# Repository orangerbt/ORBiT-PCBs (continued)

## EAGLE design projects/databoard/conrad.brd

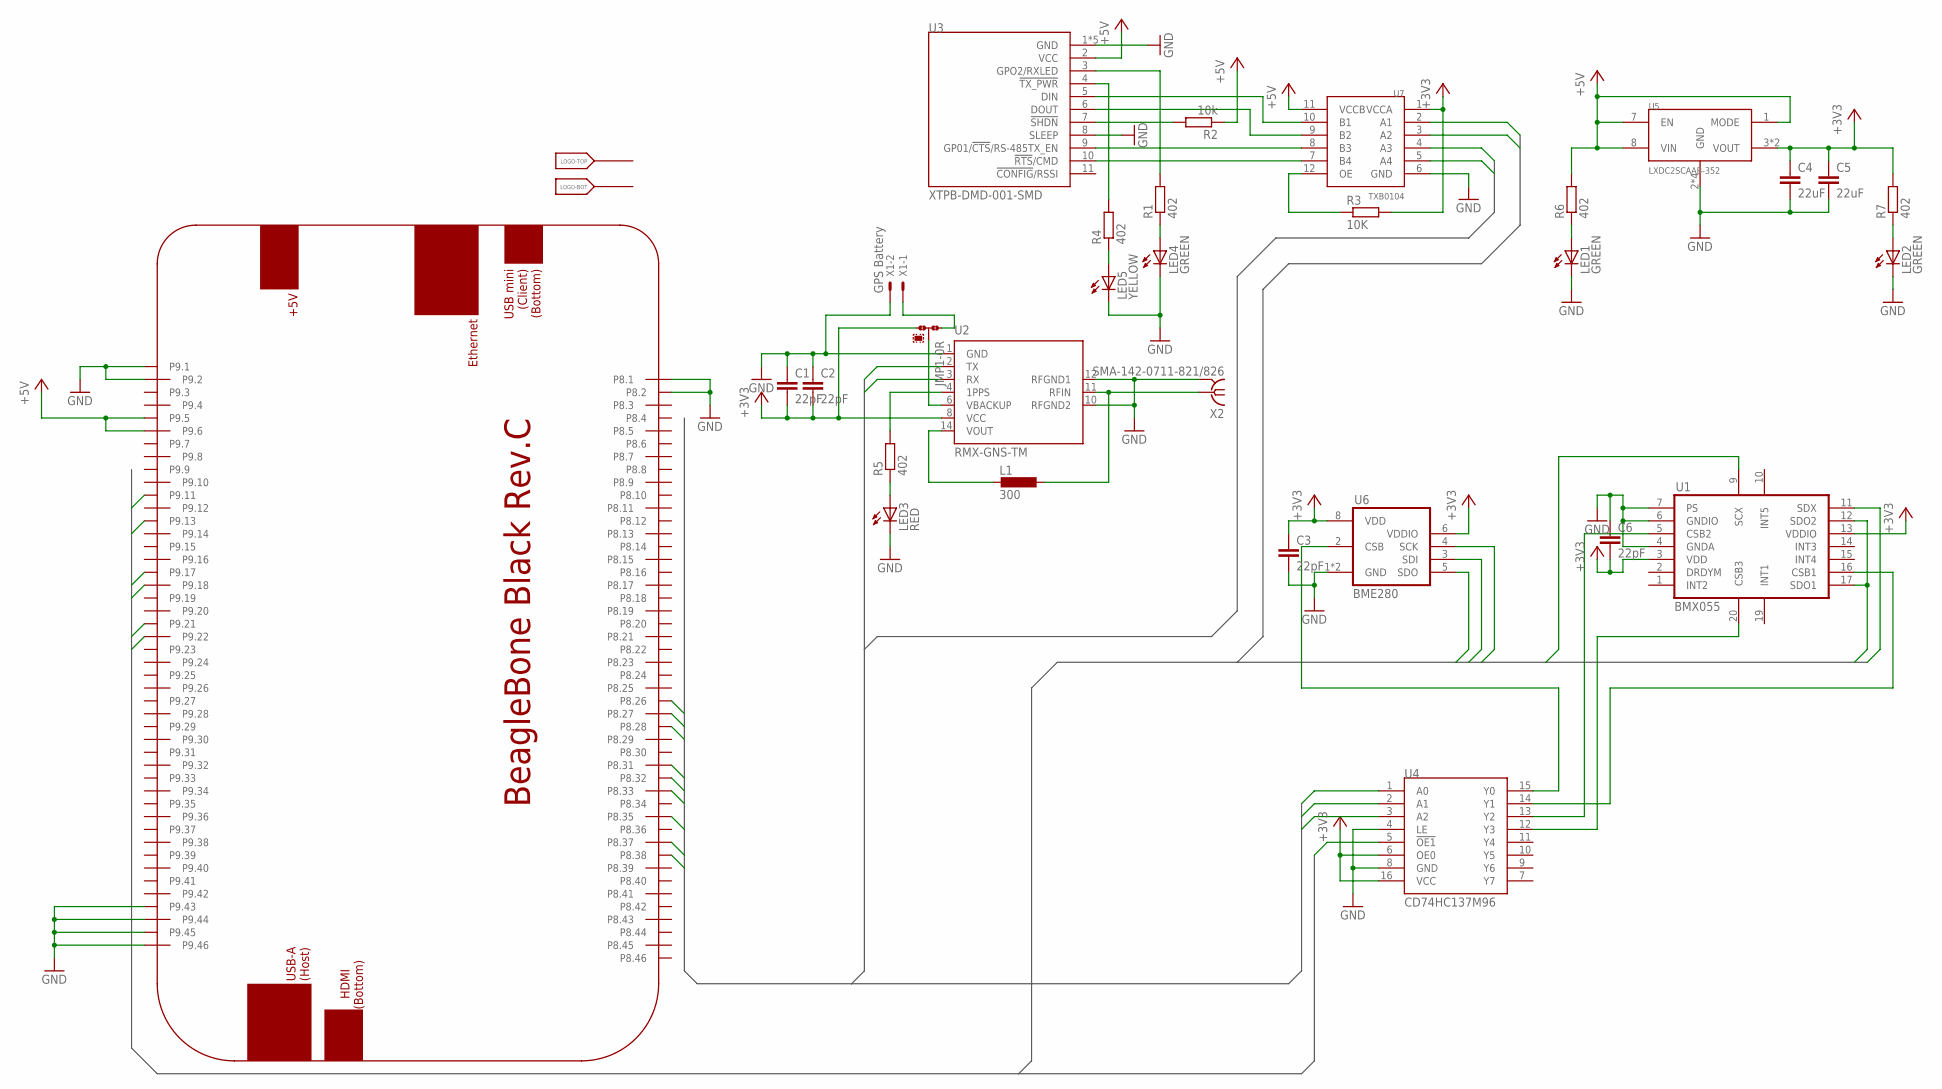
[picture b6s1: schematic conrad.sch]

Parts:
C1, C2, C3, C6: 22pF; C0603K
C4, C5: 22uF; C0603K
JMP1: 0R-JUMPB; B0R-JMP
L1: 300; L0402
LED1, LED2, LED4: GREEN; SML0805
LED3: RED; SML0805
LED5: YELLOW; SML0805
LOGO: SU_LOGO-DUMMY; SU_LOGO_DS
PCB1: BEAGLEBONE_BLACK_CAPE
R1, R4, R5, R6, R7: 402; R0603
R2: 10k; R0603
R3: 10K; R0603
U1: BMX055
U2: RMX-GNS-TM; RMX-GNSS-TM
U3: XTPB-DMD-001-SMD; XTP9B-DMS-001-SMD
U4: CD74HC137M96; SO-16
U5: LXDC2SCAAB-352
U6: BME280
U7: TXB0104; R-PUQFN-N12
X1: GPS Battery; 15-91-02
X2: SMA-142-0711-821/826; J502-ND-142-0711-821/826

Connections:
+3V3: C1.2, C2.2, C3.1, C4.1, C5.1, C6.2, JMP1.3, R3.2, R7.2, U1.3 (VDD), U1.13 (VDDIO), U2.8 (VCC), U4.6 (OE0), U4.16 (VCC), U5.3 (VOUT), U5.4 (VOUT), U6.6 (VDDIO), U6.8 (VDD), U7.1 (VCCA)
+5V: PCB1.P9.5, PCB1.P9.6, R2.1, R6.2, U3.2 (VCC), U5.1 (MODE), U5.7 (EN), U5.8 (VIN), U7.11 (VCCB)
GND: C1.1, C2.1, C3.2, C4.2, C5.2, C6.1, LED1.C, LED2.C, LED3.C, LED4.C, LED5.C, PCB1.P8.1, PCB1.P8.2, PCB1.P9.1, PCB1.P9.2, PCB1.P9.43, PCB1.P9.44, PCB1.P9.45, PCB1.P9.46, U1.4 (GNDA), U1.6 (GNDIO), U1.7 (PS), U2.1 (GND), U2.10 (RFGND2), U2.12 (RFGND1), U3.1 (GND), U3.8 (SLEEP), U3.P$1 (GND), U3.P$2 (GND), U3.P$3 (GND), U3.P$4 (GND), U4.4 (LE), U4.8 (GND), U5.2 (GND), U5.5 (GND), U5.6 (GND), U5.9 (GND), U6.1 (GND), U6.7 (GND), U7.6 (GND), X1.2, X2.G@1 (2), X2.G@2 (2), X2.G@3 (2), X2.G@4 (2)
unnamed: R3.1, U7.12 (OE)
unnamed: LED4.A, R1.1
unnamed: U3.6 (DOUT), U7.9 (B2)
unnamed: R4.2, U3.4 (!TX_PWR!)
unnamed: L1.1, U2.11 (RFIN), X2.1
unnamed: JMP1.1, X1.1
unnamed: U4.15 (Y0), U6.2 (CSB)
unnamed: U1.5 (CSB2), U4.13 (Y2)
unnamed: L1.2, U2.14 (VOUT)
unnamed: U1.16 (CSB1), U4.14 (Y1)
unnamed: R1.2, U3.3 (GPO2/RXLED)
unnamed: U1.20 (CSB3), U4.12 (Y3)
unnamed: R5.2, U2.4 (1PPS)
unnamed: LED5.A, R4.1
unnamed: R2.2, U3.7 (!SHDN!)
unnamed: LED3.A, R5.1
unnamed: LED1.A, R6.1
unnamed: LED2.A, R7.1
SPI0_CS0: PCB1.P9.17, U4.5 (!OE1!)
SPI0_D0: PCB1.P9.21, U1.12 (SDO2), U1.17 (SDO1), U6.5 (SDO)
SPI0_D1: PCB1.P9.18, U1.11 (SDX), U6.3 (SDI)
SPI0_SCLK: PCB1.P9.22, U1.9 (SCX), U6.4 (SCK)
SPI_CSB26: PCB1.P8.26, U4.1 (A0)
SPI_CSB27: PCB1.P8.27, U4.2 (A1)
SPI_CSB28: PCB1.P8.28, U4.3 (A2)
UART4_CTSN: PCB1.P8.35, U7.4 (A3)
UART4_CTSN_HV: U3.9 (GP01/!CTS!/RS-485TX_EN), U7.8 (B3)
UART4_RTSN: PCB1.P8.33, U7.5 (A4)
UART4_RTSN_HV: U3.10 (!RTS!/CMD), U7.7 (B4)
UART4_RXD: PCB1.P9.11, U7.3 (A2)
UART4_TXD: PCB1.P9.13, U7.2 (A1)
UART4_TXD-HV: U3.5 (DIN), U7.10 (B1)
UART5_CTSN: PCB1.P8.31
UART5_RTSN: PCB1.P8.32
UART5_RXD: PCB1.P8.38, U2.2 (TX)
UART5_TXD: PCB1.P8.37, U2.3 (RX)
VBACKUP: JMP1.2, U2.6 (VBACKUP)

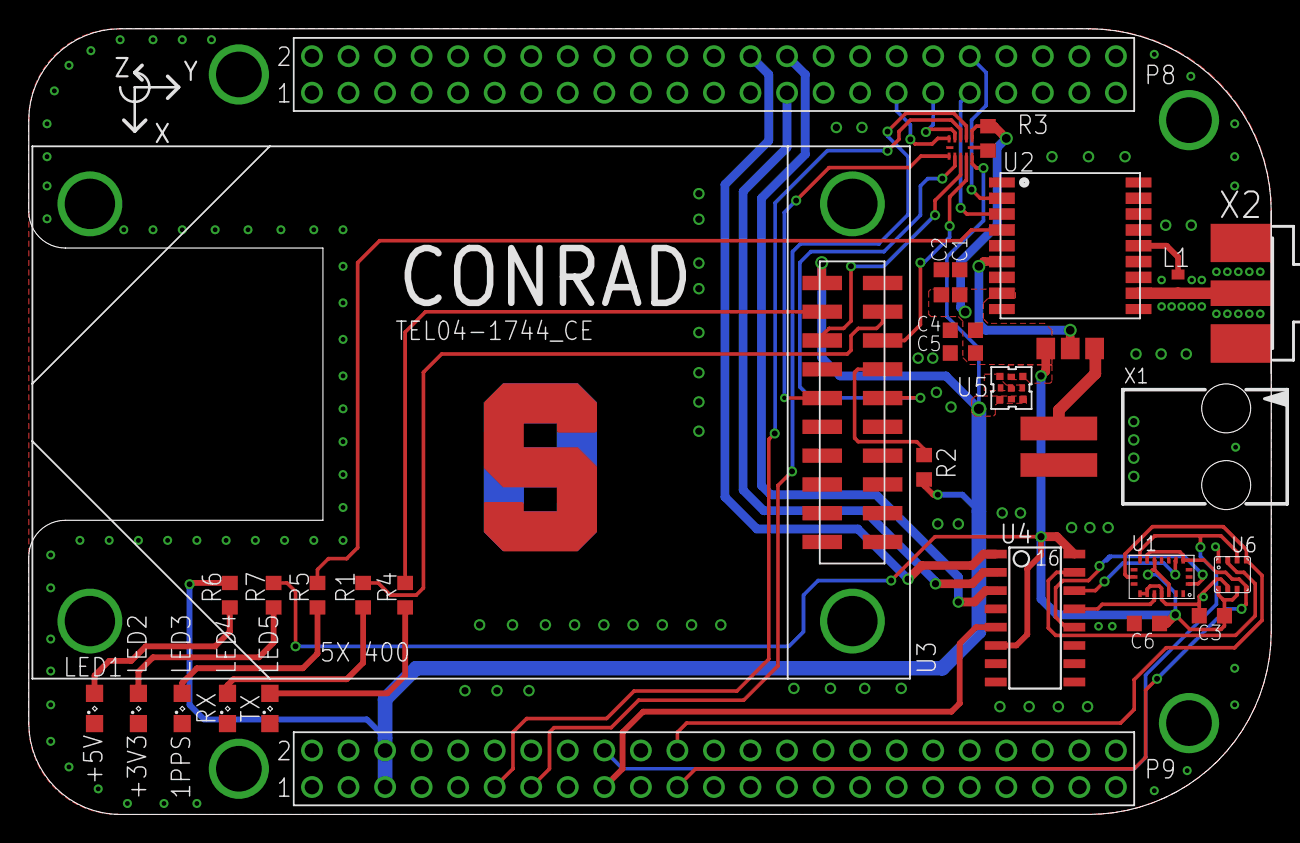
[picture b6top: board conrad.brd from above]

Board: 2 copper layers, 86.4 x 54.6 mm, 31 parts (0 on the bottom side), 38 nets.

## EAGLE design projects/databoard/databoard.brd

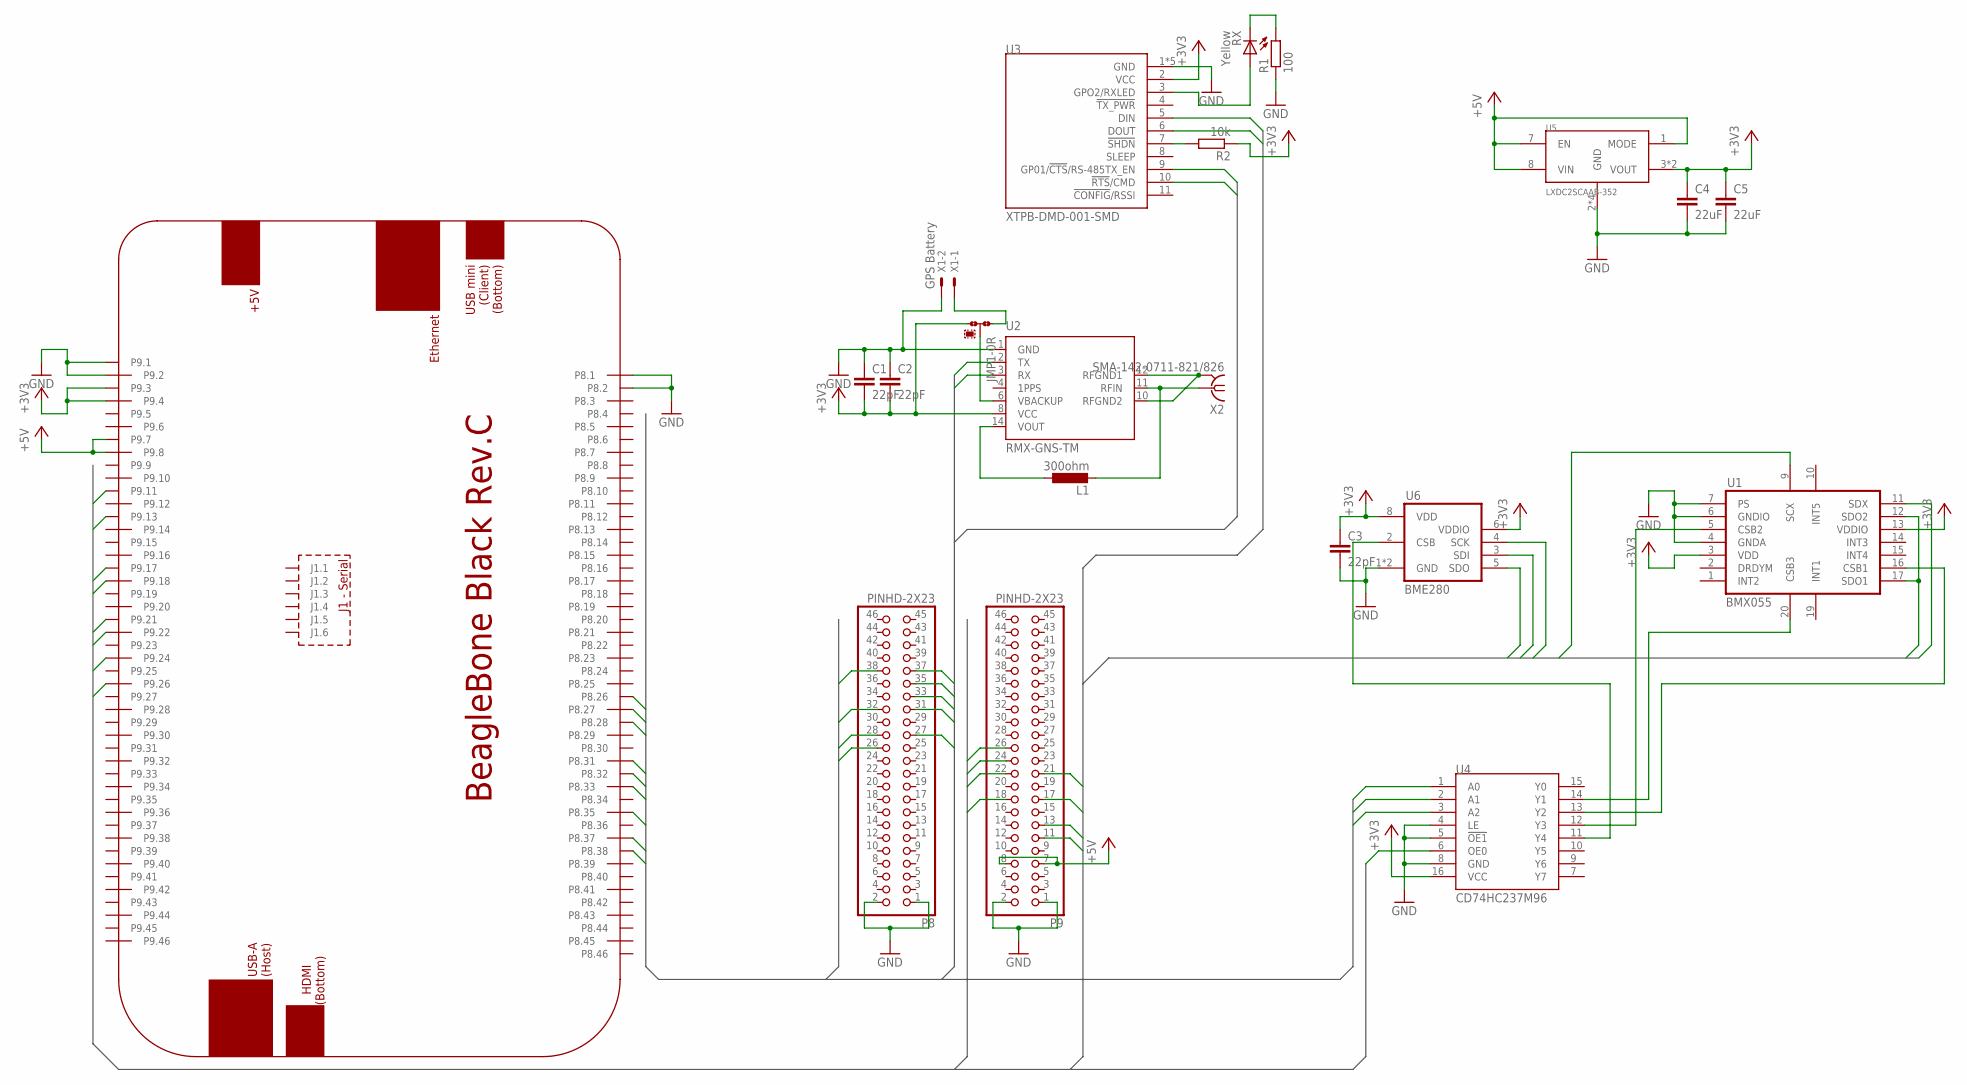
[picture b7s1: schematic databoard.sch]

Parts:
C1, C2, C3: 22pF; C0603K
C4, C5: 22uF; C0603K
JMP1: 0R-JUMPB; B0R-JMP
L1: 300ohm; L1206
P8, P9: PINHD-2X23; 2X23
R1: 100; R0402
R2: 10k; R0402
RX: Yellow; SML0805
U1: BMX055
U2: RMX-GNS-TM; RMX-GNSS-TM
U3: XTPB-DMD-001-SMD; XTP9B-DMS-001-SMD
U4: CD74HC237M96; SO-16
U5: LXDC2SCAAB-352
U6: BME280
X1: GPS Battery; 15-91-02
X2: SMA-142-0711-821/826; J502-ND-142-0711-821/826

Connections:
+3V3: C1.2, C2.2, C3.1, C4.1, C5.1, JMP1.3, R2.1, U1.3 (VDD), U1.13 (VDDIO), U2.8 (VCC), U3.2 (VCC), U4.16 (VCC), U5.3 (VOUT), U5.4 (VOUT), U6.6 (VDDIO), U6.8 (VDD)
+5V: P9.7, P9.8, U5.1 (MODE), U5.7 (EN), U5.8 (VIN)
GND: C1.1, C2.1, C3.2, C4.2, C5.2, P8.1, P8.2, P9.1, P9.2, R1.1, U1.4 (GNDA), U1.6 (GNDIO), U1.7 (PS), U2.1 (GND), U3.1 (GND), U3.P$1 (GND), U3.P$2 (GND), U3.P$3 (GND), U3.P$4 (GND), U4.4 (LE), U4.5 (!OE1!), U4.8 (GND), U5.2 (GND), U5.5 (GND), U5.6 (GND), U5.9 (GND), U6.1 (GND), U6.7 (GND), X1.2
I2C1_SCL: P9.24
I2C1_SDA: P9.26
unnamed: L1.2, U2.11 (RFIN), X2.1
unnamed: JMP1.1, X1.1
unnamed: U4.11 (Y4), U6.2 (CSB)
unnamed: U1.5 (CSB2), U4.12 (Y3)
unnamed: L1.1, U2.14 (VOUT)
unnamed: U1.16 (CSB1), U4.13 (Y2)
unnamed: RX.A, U3.3 (GPO2/RXLED)
unnamed: U1.20 (CSB3), U4.14 (Y1)
unnamed: R1.2, RX.C
unnamed: R2.2, U3.7 (!SHDN!)
RFGND1: U2.10 (RFGND2), U2.12 (RFGND1), X2.G@1 (2), X2.G@2 (2), X2.G@3 (2), X2.G@4 (2)
SPI0_CS0: P9.17, U4.6 (OE0)
SPI0_D0: P9.21, U1.12 (SDO2), U1.17 (SDO1), U6.5 (SDO)
SPI0_D1: P9.18, U1.11 (SDX), U6.3 (SDI)
SPI0_SCLK: P9.22, U1.9 (SCX), U6.4 (SCK)
SPI_CSB26: P8.26, U4.1 (A0)
SPI_CSB27: P8.27, U4.2 (A1)
SPI_CSB28: P8.28, U4.3 (A2)
UART4_CTSN: P8.35, U3.9 (GP01/!CTS!/RS-485TX_EN)
UART4_RTSN: P8.33, U3.10 (!RTS!/CMD)
UART4_RXD: P9.11, U3.6 (DOUT)
UART4_TXD: P9.13, U3.5 (DIN)
UART5_CTSN: P8.31
UART5_RTSN: P8.32
UART5_RXD: P8.38, U2.3 (RX)
UART5_TXD: P8.37, U2.2 (TX)
VBACKUP: JMP1.2, U2.6 (VBACKUP)

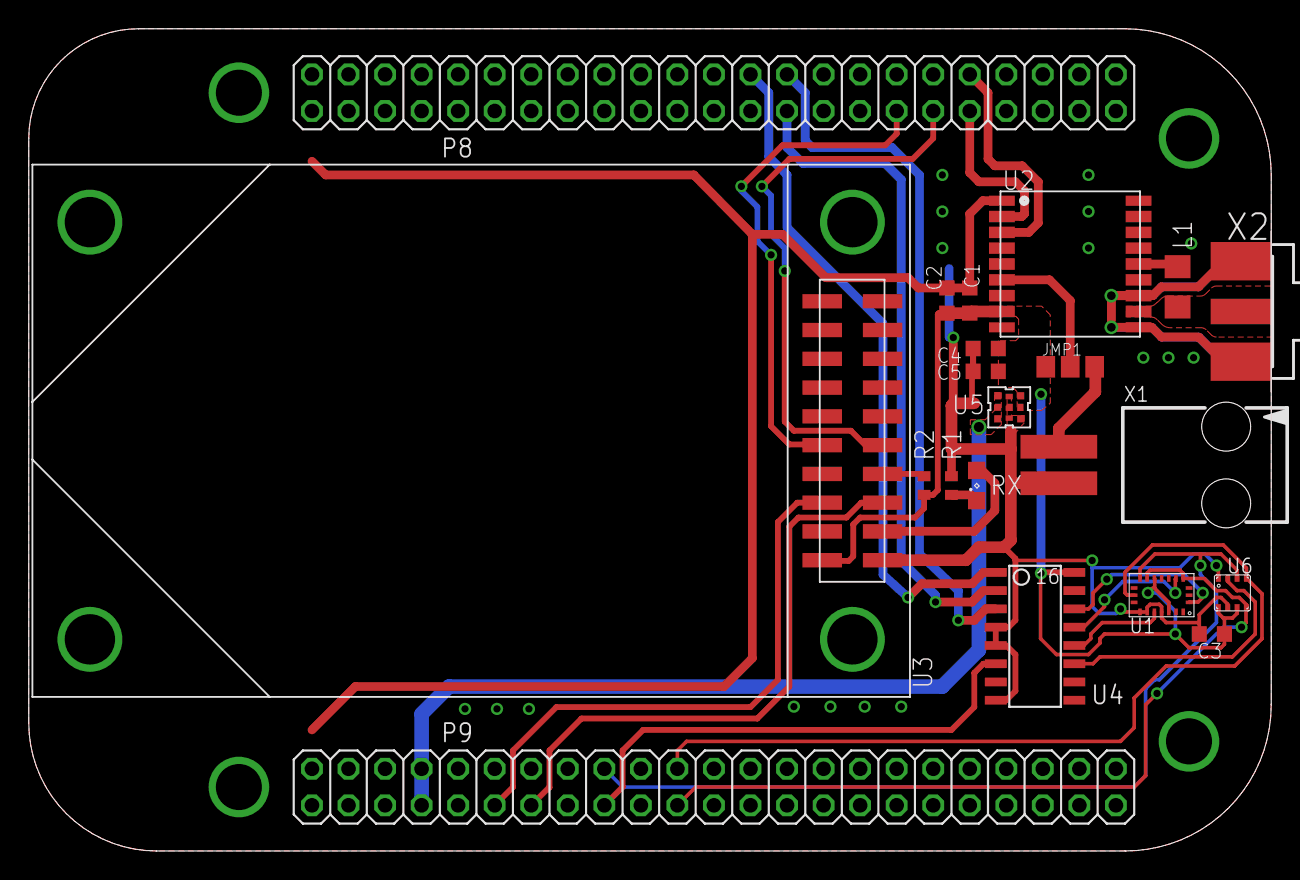
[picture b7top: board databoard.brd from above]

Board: 2 copper layers, 86.4 x 57.2 mm, 20 parts (0 on the bottom side), 28 nets.

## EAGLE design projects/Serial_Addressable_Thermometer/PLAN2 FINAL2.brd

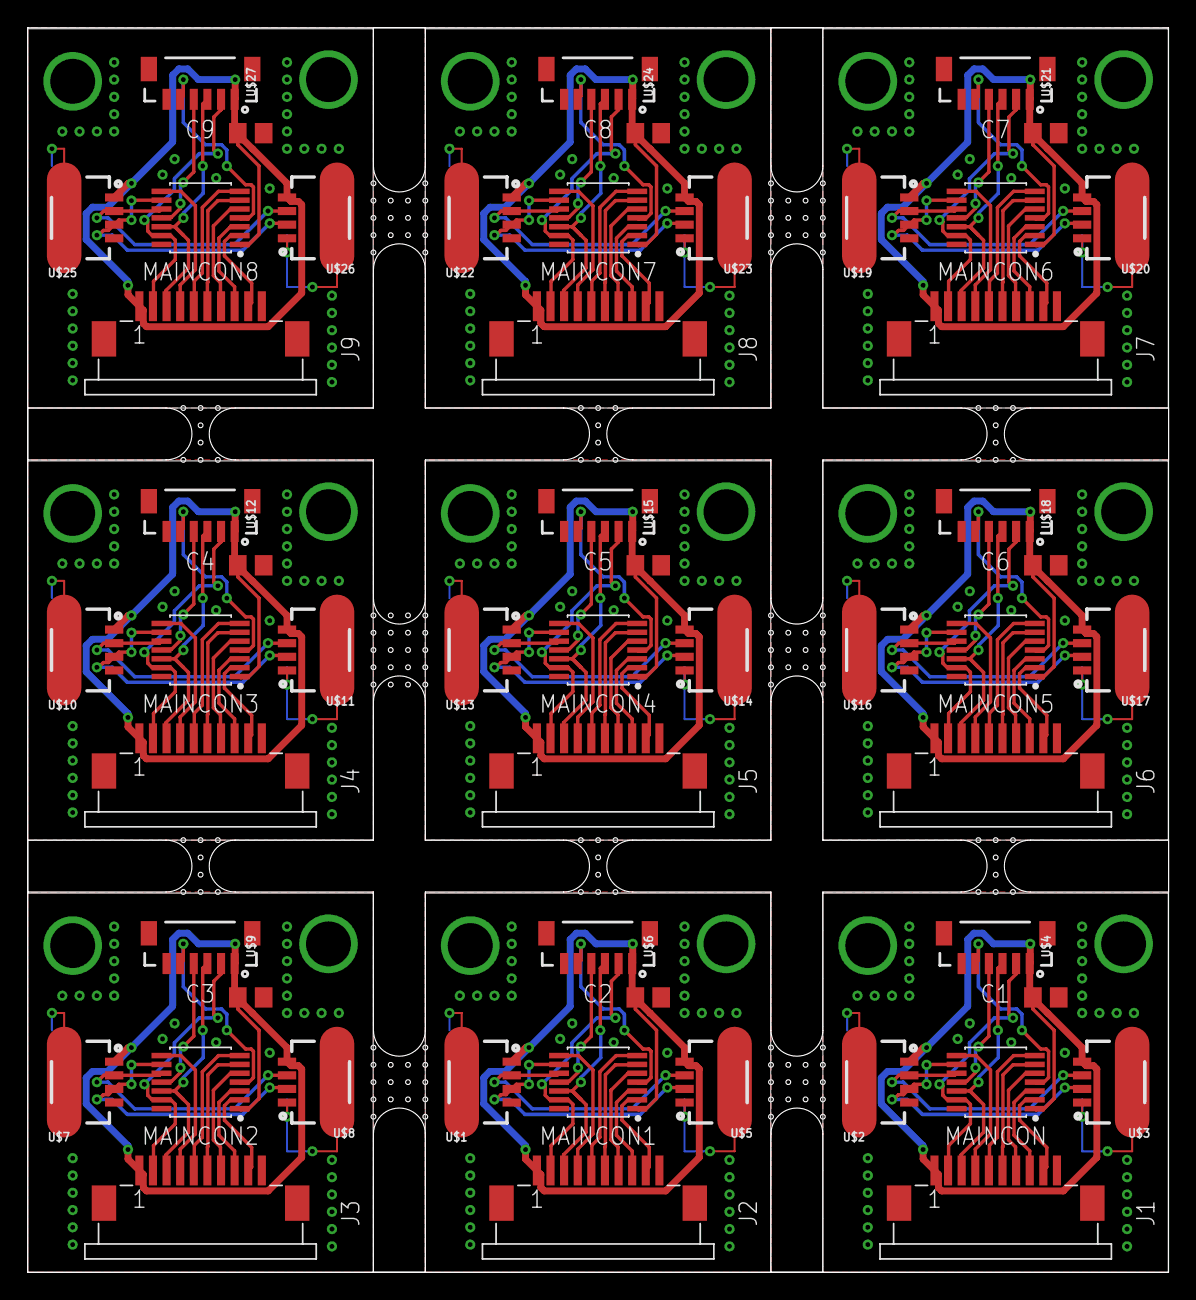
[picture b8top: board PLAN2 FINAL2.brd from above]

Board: 2 copper layers, 83.8 x 91.4 mm, 54 parts (0 on the bottom side), 126 nets.

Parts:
C1, C2, C3, C4, C5, C6, C7, C8, C9: 47u; C0805
J1, J2, J3, J4, J5, J6, J7, J8, J9: analog; 68611014422
MAINCON, MAINCON1, MAINCON2, MAINCON3, MAINCON4, MAINCON5, MAINCON6, MAINCON7, MAINCON8: PIC16F18424; 14-TSSOP
U$1, U$2, U$7, U$10, U$13, U$16, U$19, U$22, U$25: IIC1; JST_ZH_4PIN
U$3, U$5, U$8, U$11, U$14, U$17, U$20, U$23, U$26: IIC2; JST_ZH_4PIN
U$4, U$6, U$9, U$12, U$15, U$18, U$21, U$24, U$27: programming; JST_ZH_6PIN

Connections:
+5V: C1.1, J1.1, MAINCON.1, U$2.1, U$3.4, U$4.1
+5V1: C2.1, J2.1, MAINCON1.1, U$1.1, U$5.4, U$6.1
+5V2: C3.1, J3.1, MAINCON2.1, U$7.1, U$8.4, U$9.1
+5V3: C4.1, J4.1, MAINCON3.1, U$10.1, U$11.4, U$12.1
+5V4: C5.1, J5.1, MAINCON4.1, U$13.1, U$14.4, U$15.1
+5V5: C6.1, J6.1, MAINCON5.1, U$16.1, U$17.4, U$18.1
+5V6: C7.1, J7.1, MAINCON6.1, U$19.1, U$20.4, U$21.1
+5V7: C8.1, J8.1, MAINCON7.1, U$22.1, U$23.4, U$24.1
+5V8: C9.1, J9.1, MAINCON8.1, U$25.1, U$26.4, U$27.1
AD1: J1.2, MAINCON.13, U$4.2
AD2: J1.3, MAINCON.12, U$4.3
AD3: J1.4, MAINCON.8
AD4: J1.5, MAINCON.7
AD5: J1.6, MAINCON.6
AD6: J1.7, MAINCON.5
AD7: J1.8, MAINCON.3
AD8: J1.9, MAINCON.2
AD9: J2.4, MAINCON1.8
AD10: J2.5, MAINCON1.7
AD11: J2.6, MAINCON1.6
AD12: J2.7, MAINCON1.5
AD13: J2.8, MAINCON1.3
AD14: J2.9, MAINCON1.2
AD15: J2.2, MAINCON1.13, U$6.2
AD16: J2.3, MAINCON1.12, U$6.3
AD17: J3.4, MAINCON2.8
AD18: J3.5, MAINCON2.7
AD19: J3.6, MAINCON2.6
AD20: J3.7, MAINCON2.5
AD21: J3.8, MAINCON2.3
AD22: J3.9, MAINCON2.2
AD23: J3.2, MAINCON2.13, U$9.2
AD24: J3.3, MAINCON2.12, U$9.3
AD25: J4.4, MAINCON3.8
AD26: J4.5, MAINCON3.7
AD27: J4.6, MAINCON3.6
AD28: J4.7, MAINCON3.5
AD29: J4.8, MAINCON3.3
AD30: J4.9, MAINCON3.2
AD31: J4.2, MAINCON3.13, U$12.2
AD32: J4.3, MAINCON3.12, U$12.3
AD33: J5.4, MAINCON4.8
AD34: J5.5, MAINCON4.7
AD35: J5.6, MAINCON4.6
AD36: J5.7, MAINCON4.5
AD37: J5.8, MAINCON4.3
AD38: J5.9, MAINCON4.2
AD39: J5.2, MAINCON4.13, U$15.2
AD40: J5.3, MAINCON4.12, U$15.3
AD41: J6.4, MAINCON5.8
AD42: J6.5, MAINCON5.7
AD43: J6.6, MAINCON5.6
AD44: J6.7, MAINCON5.5
AD45: J6.8, MAINCON5.3
AD46: J6.9, MAINCON5.2
AD47: J6.2, MAINCON5.13, U$18.2
AD48: J6.3, MAINCON5.12, U$18.3
AD49: J7.4, MAINCON6.8
AD50: J7.5, MAINCON6.7
AD51: J7.6, MAINCON6.6
AD52: J7.7, MAINCON6.5
AD53: J7.8, MAINCON6.3
AD54: J7.9, MAINCON6.2
AD55: J7.2, MAINCON6.13, U$21.2
AD56: J7.3, MAINCON6.12, U$21.3
AD57: J8.4, MAINCON7.8
AD58: J8.5, MAINCON7.7
AD59: J8.6, MAINCON7.6
AD60: J8.7, MAINCON7.5
AD61: J8.8, MAINCON7.3
AD62: J8.9, MAINCON7.2
AD63: J8.2, MAINCON7.13, U$24.2
AD64: J8.3, MAINCON7.12, U$24.3
AD65: J9.4, MAINCON8.8
AD66: J9.5, MAINCON8.7
AD67: J9.6, MAINCON8.6
AD68: J9.7, MAINCON8.5
AD69: J9.8, MAINCON8.3
AD70: J9.9, MAINCON8.2
AD71: J9.2, MAINCON8.13, U$27.2
AD72: J9.3, MAINCON8.12, U$27.3
GND: C1.2, J1.10, MAINCON.14, U$2.4, U$2.NC1, U$2.NC2, U$3.1, U$3.NC1, U$3.NC2, U$4.6, U$4.P$1
GND1: C2.2, J2.10, MAINCON1.14, U$1.4, U$1.NC1, U$1.NC2, U$5.1, U$5.NC1, U$5.NC2, U$6.6, U$6.P$1
GND2: C3.2, J3.10, MAINCON2.14, U$7.4, U$7.NC1, U$7.NC2, U$8.1, U$8.NC1, U$8.NC2, U$9.6, U$9.P$1
GND3: C4.2, J4.10, MAINCON3.14, U$10.4, U$10.NC1, U$10.NC2, U$11.1, U$11.NC1, U$11.NC2, U$12.6, U$12.P$1
GND4: C5.2, J5.10, MAINCON4.14, U$13.4, U$13.NC1, U$13.NC2, U$14.1, U$14.NC1, U$14.NC2, U$15.6, U$15.P$1
GND5: C6.2, J6.10, MAINCON5.14, U$16.4, U$16.NC1, U$16.NC2, U$17.1, U$17.NC1, U$17.NC2, U$18.6, U$18.P$1
GND6: C7.2, J7.10, MAINCON6.14, U$19.4, U$19.NC1, U$19.NC2, U$20.1, U$20.NC1, U$20.NC2, U$21.6, U$21.P$1
GND7: C8.2, J8.10, MAINCON7.14, U$22.4, U$22.NC1, U$22.NC2, U$23.1, U$23.NC1, U$23.NC2, U$24.6, U$24.P$1
GND8: C9.2, J9.10, MAINCON8.14, U$25.4, U$25.NC1, U$25.NC2, U$26.1, U$26.NC1, U$26.NC2, U$27.6, U$27.P$1
unnamed: MAINCON1.11, U$6.4
unnamed: MAINCON1.4, U$6.5
unnamed: MAINCON.11, U$4.4
unnamed: MAINCON.4, U$4.5
unnamed: MAINCON2.11, U$9.4
unnamed: MAINCON2.4, U$9.5
unnamed: MAINCON3.11, U$12.4
unnamed: MAINCON3.4, U$12.5
unnamed: MAINCON4.11, U$15.4
unnamed: MAINCON4.4, U$15.5
unnamed: MAINCON5.11, U$18.4
unnamed: MAINCON5.4, U$18.5
unnamed: MAINCON6.11, U$21.4
unnamed: MAINCON6.4, U$21.5
unnamed: MAINCON7.11, U$24.4
unnamed: MAINCON7.4, U$24.5
unnamed: MAINCON8.11, U$27.4
unnamed: MAINCON8.4, U$27.5
SCL: MAINCON.10, U$2.2, U$3.3
SCL1: MAINCON1.10, U$1.2, U$5.3
SCL2: MAINCON2.10, U$7.2, U$8.3
SCL3: MAINCON3.10, U$10.2, U$11.3
SCL4: MAINCON4.10, U$13.2, U$14.3
SCL5: MAINCON5.10, U$16.2, U$17.3
SCL6: MAINCON6.10, U$19.2, U$20.3
SCL7: MAINCON7.10, U$22.2, U$23.3
SCL8: MAINCON8.10, U$25.2, U$26.3
SDA: MAINCON.9, U$2.3, U$3.2
SDA1: MAINCON1.9, U$1.3, U$5.2
SDA2: MAINCON2.9, U$7.3, U$8.2
SDA3: MAINCON3.9, U$10.3, U$11.2
SDA4: MAINCON4.9, U$13.3, U$14.2
SDA5: MAINCON5.9, U$16.3, U$17.2
SDA6: MAINCON6.9, U$19.3, U$20.2
SDA7: MAINCON7.9, U$22.3, U$23.2
SDA8: MAINCON8.9, U$25.3, U$26.2

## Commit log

2018-03-31 Initial commit.
2018-04-07 Fixed board outline on actuator board.
2018-05-05 Added sensors library.
2018-10-06 Add readme Merge old PCB repository
2018-10-13 Some stuff
2018-10-13 Fuses, inductors, transistors
2018-10-19 Better libraries More readme info
2018-10-19 Actuator board
    lotta work done on actuator board
2018-10-20 Molex Nano-Fit CAT24C256 EEPROM
2018-10-20 Added Maxim RTCs
2018-10-20 Finished (?) libraries
2018-10-21 Started new telemetry schematics
2019-03-20 init
2019-03-20 add part list
2019-03-21 add STM32F042 lib
2019-03-24 add pic controllor
2019-03-25 fix name
2019-03-26 finish SAT board and temp sensor
2019-03-27 add final board file
2019-03-28 add card edge
2019-03-28 clean cache
2019-03-28 fix stm32
2019-03-29 add JST connector lib
2019-03-30 add RUDAS ram cpld
2019-03-30 add STM32 micro controller
2019-03-31 rename
2019-03-31 add connection
2019-04-02 add connector
2019-04-03 add new part list
2019-04-04 chage
2019-04-07 add part list and fix package problem
2019-04-09 garber finish
2019-04-11 add connector info
2019-04-18 add powersupply
2019-06-08 Lots of updates not committed
2019-06-15 Finished basic functionality for telemetry board
2019-06-18 add ddr3 memory and cyclone v soc
2019-06-20 add RUDAS base design block
2019-06-20 add ref design
2019-07-11 CONRAD - Added test points
2019-09-08 CONRAD - adding LTC6820 for isolated SPI sensors
